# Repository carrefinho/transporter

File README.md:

# Transporter

Transporter is a low-profile V4N4G0N type keyboard with exploded bars, built around the $0.5 WCH CH32X035 MCU.

## Files

- [`transporter-pcb/`](transporter-pcb/): KiCad project
    - [Interactive BOM](transporter-pcb/bom/ibom.html)
    - [JLCPCB production files](transporter-pcb/jlcpcb/production_files/)
    - [View the PCB on KiCanvas](https://kicanvas.org/?github=https%3A%2F%2Fgithub.com%2Fcarrefinho%2Ftransporter%2Ftree%2Fmain%2Ftransporter-pcb)
- [`case/facade/`](case/facade/): Facade v4 case files

## Firmware

Find the ZMK module at [transporter-zmk-module](https://github.com/carrefinho/transporter-zmk-module)

## License

[CERN-OHL-P v2](LICENSE)

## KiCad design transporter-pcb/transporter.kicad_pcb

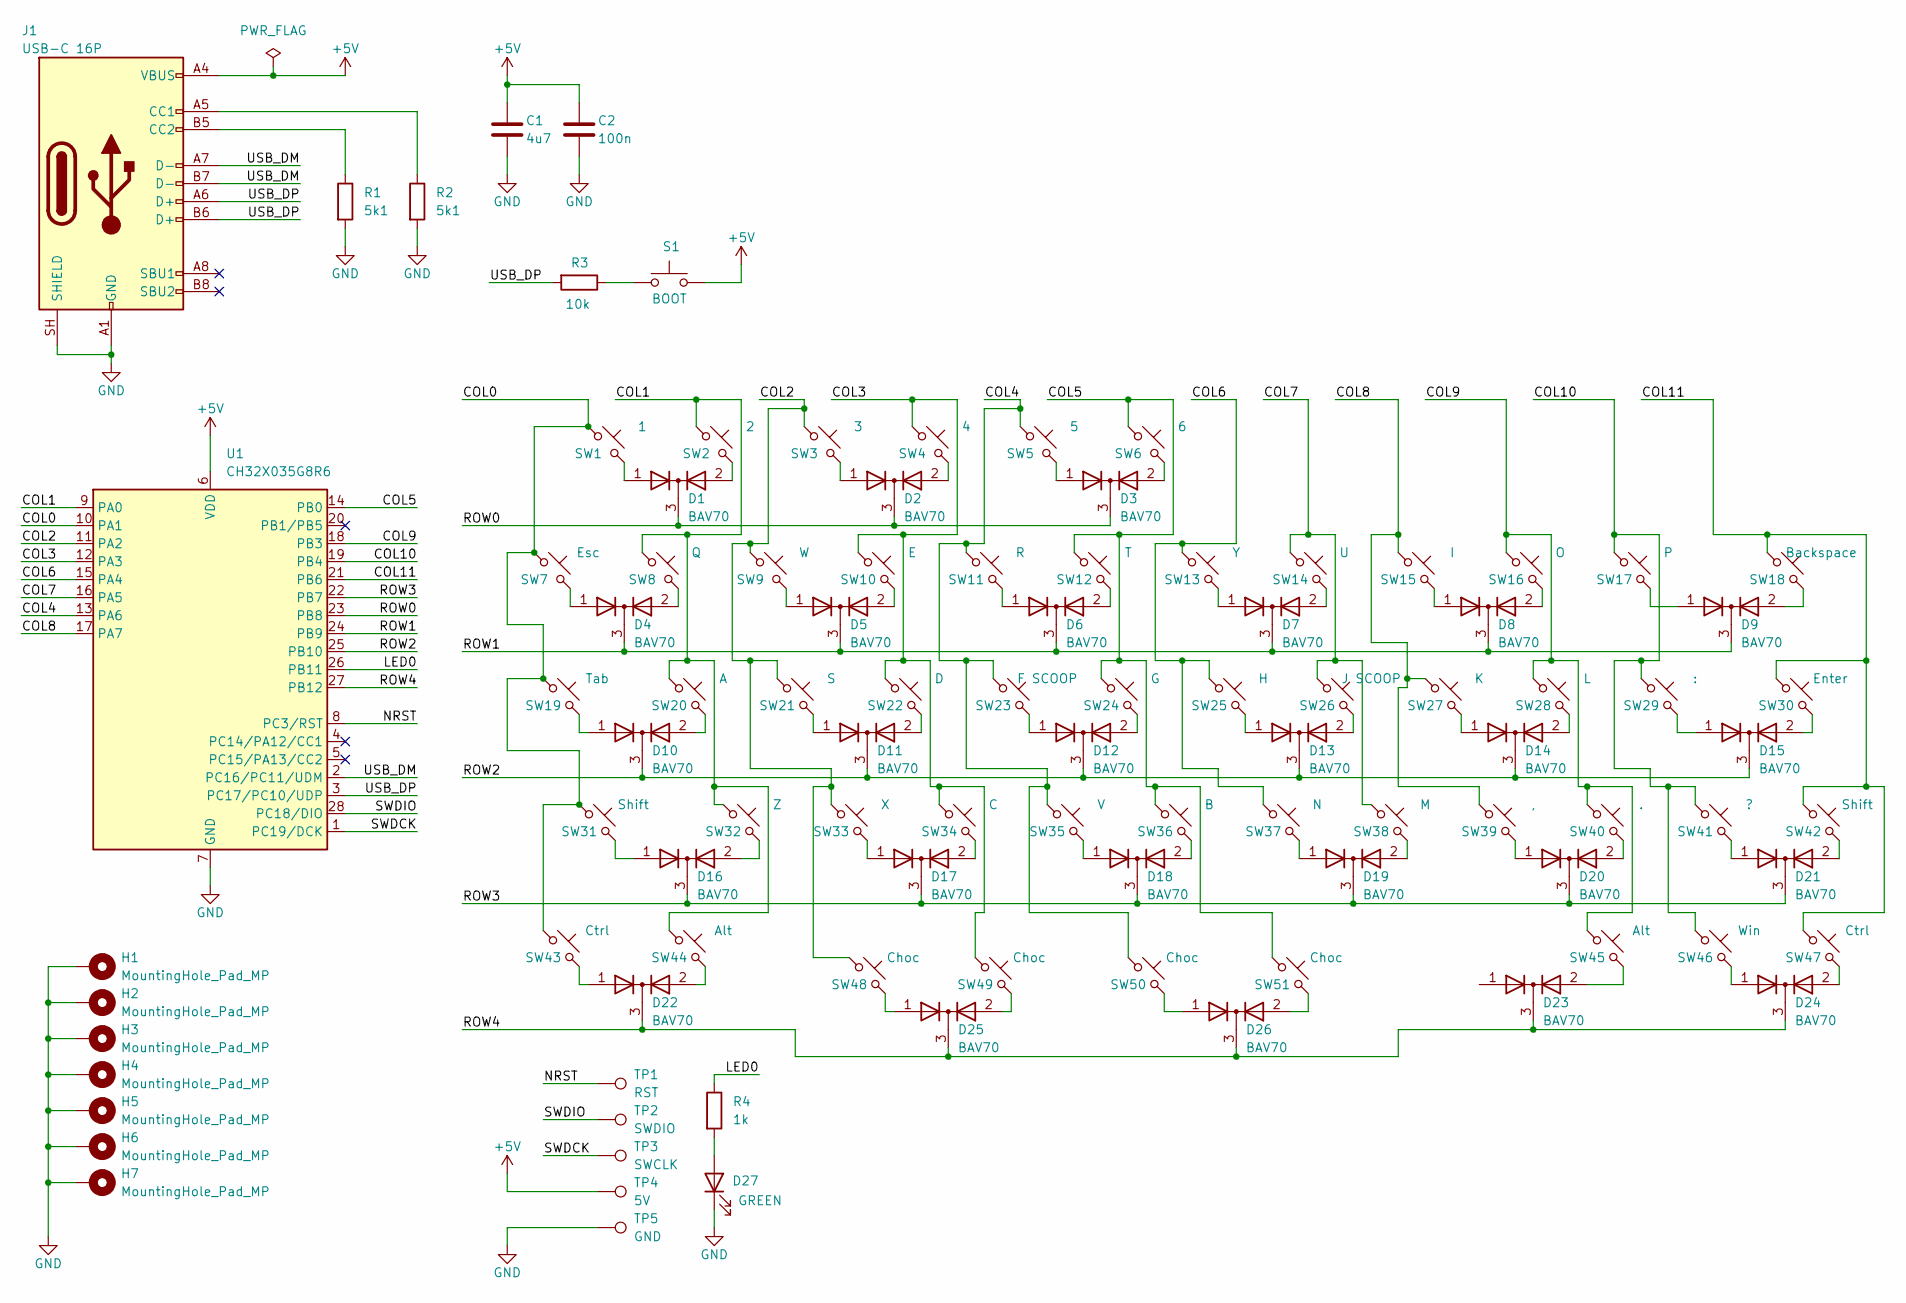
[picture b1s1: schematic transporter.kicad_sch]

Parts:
C1: 4u7; C_0805_2012Metric
C2: 100n; C_0603_1608Metric
D1, D2, D3, D4, D5, D6, D7, D8, D9, D10, D11, D12, D13, D14, D15, D16, D17, D18, D19, D20, D21, D22, D23, D24, D25, D26: BAV70; SOT-23
D27: GREEN; LED_0805_2012Metric
H1, H2, H3, H4, H5, H6, H7: MountingHole_Pad_MP; MountingHole_2.2mm_M2_Pad_TopBottom
J1: USB-C 16P; USB_C_Receptacle_G-Switch_GT-USB-7010ASV
R1, R2: 5k1; R_0603_1608Metric
R3: 10k; R_0603_1608Metric
R4: 1k; R_0603_1608Metric
S1: BOOT; SW_SPST_TS-1088-xR020
SW1: 1; SW_choc_v1v2_HS_19mmSpc
SW2: 2; SW_choc_v1v2_HS_19mmSpc
SW3: 3; SW_choc_v1v2_HS_19mmSpc
SW4: 4; SW_choc_v1v2_HS_19mmSpc
SW5: 5; SW_choc_v1v2_HS_19mmSpc
SW6: 6; SW_choc_v1v2_HS_19mmSpc
SW7: Esc; SW_choc_v1v2_HS_19mmSpc
SW8: Q; SW_choc_v1v2_HS_19mmSpc
SW9: W; SW_choc_v1v2_HS_19mmSpc
SW10: E; SW_choc_v1v2_HS_19mmSpc
SW11: R; SW_choc_v1v2_HS_19mmSpc
SW12: T; SW_choc_v1v2_HS_19mmSpc
SW13: Y; SW_choc_v1v2_HS_19mmSpc
SW14: U; SW_choc_v1v2_HS_19mmSpc
SW15: I; SW_choc_v1v2_HS_19mmSpc
SW16: O; SW_choc_v1v2_HS_19mmSpc
SW17: P; SW_choc_v1v2_HS_19mmSpc
SW18: Backspace; SW_choc_v1v2_HS_19mmSpc
SW19: Tab; SW_choc_v1v2_HS_19mmSpc
SW20: A; SW_choc_v1v2_HS_19mmSpc
SW21: S; SW_choc_v1v2_HS_19mmSpc
SW22: D; SW_choc_v1v2_HS_19mmSpc
SW23: F SCOOP; SW_choc_v1v2_HS_19mmSpc
SW24: G; SW_choc_v1v2_HS_19mmSpc
SW25: H; SW_choc_v1v2_HS_19mmSpc
SW26: J SCOOP; SW_choc_v1v2_HS_19mmSpc
SW27: K; SW_choc_v1v2_HS_19mmSpc
SW28: L; SW_choc_v1v2_HS_19mmSpc
SW29: :; SW_choc_v1v2_HS_19mmSpc
SW30: Enter; SW_choc_v1v2_HS_19mmSpc
SW31, SW42: Shift; SW_choc_v1v2_HS_19mmSpc
SW32: Z; SW_choc_v1v2_HS_19mmSpc
SW33: X; SW_choc_v1v2_HS_19mmSpc
SW34: C; SW_choc_v1v2_HS_19mmSpc
SW35: V; SW_choc_v1v2_HS_19mmSpc
SW36: B; SW_choc_v1v2_HS_19mmSpc
SW37: N; SW_choc_v1v2_HS_19mmSpc
SW38: M; SW_choc_v1v2_HS_19mmSpc
SW39: ,; SW_choc_v1v2_HS_19mmSpc
SW40: .; SW_choc_v1v2_HS_19mmSpc
SW41: ?; SW_choc_v1v2_HS_19mmSpc
SW43, SW47: Ctrl; SW_choc_v1v2_HS_19mmSpc
SW44, SW45: Alt; SW_choc_v1v2_HS_19mmSpc
SW46: Win; SW_choc_v1v2_HS_19mmSpc
SW48, SW49, SW50, SW51: Choc; SW_choc_v1v2_HS_19mmSpc
TP1: RST; TestPoint_Pad_D2.0mm
TP2: SWDIO; TestPoint_Pad_D2.0mm
TP3: SWCLK; TestPoint_Pad_D2.0mm
TP4: 5V; TestPoint_Pad_D2.0mm
TP5: GND; TestPoint_Pad_D2.0mm
U1: CH32X035G8R6; QSOP-28_3.9x9.9mm_P0.635mm

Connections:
+5V: C1.1, C2.1, J1.A4 (VBUS), J1.A9 (VBUS), J1.B4 (VBUS), J1.B9 (VBUS), S1.2, TP4.1 (1_1), U1.6 (VDD)
/COL0: SW1.1, SW7.1, SW19.1, SW31.1, SW43.1, U1.10 (PA1)
/COL1: SW2.1, SW8.1, SW20.1, SW32.1, SW44.1, U1.9 (PA0)
/COL2: SW3.1, SW9.1, SW21.1, SW33.1, SW48.1, U1.11 (PA2)
/COL3: SW4.1, SW10.1, SW22.1, SW34.1, SW49.1, U1.12 (PA3)
/COL4: SW5.1, SW11.1, SW23.1, SW35.1, SW50.1, U1.13 (PA6)
/COL5: SW6.1, SW12.1, SW24.1, SW36.1, SW51.1, U1.14 (PB0)
/COL6: SW13.1, SW25.1, SW37.1, U1.15 (PA4)
/COL7: SW14.1, SW26.1, SW38.1, U1.16 (PA5)
/COL8: SW15.1, SW27.1, SW39.1, U1.17 (PA7)
/COL9: SW16.1, SW28.1, SW40.1, SW45.1, U1.18 (PB3)
/COL10: SW17.1, SW29.1, SW41.1, SW46.1, U1.19 (PB4)
/COL11: SW18.1, SW30.1, SW42.1, SW47.1, U1.21 (PB6)
/LED0: R4.1, U1.26 (PB11)
/NRST: TP1.1 (1_1), U1.8 (PC3/RST)
/ROW0: D1.3 (K), D2.3 (K), D3.3 (K), U1.23 (PB8)
/ROW1: D4.3 (K), D5.3 (K), D6.3 (K), D7.3 (K), D8.3 (K), D9.3 (K), U1.24 (PB9)
/ROW2: D10.3 (K), D11.3 (K), D12.3 (K), D13.3 (K), D14.3 (K), D15.3 (K), U1.25 (PB10)
/ROW3: D16.3 (K), D17.3 (K), D18.3 (K), D19.3 (K), D20.3 (K), D21.3 (K), U1.22 (PB7)
/ROW4: D22.3 (K), D23.3 (K), D24.3 (K), D25.3 (K), D26.3 (K), U1.27 (PB12)
/SWDCK: TP3.1 (1_1), U1.1 (PC19/DCK)
/SWDIO: TP2.1 (1_1), U1.28 (PC18/DIO)
/USB_DM: J1.A7 (D-), J1.B7 (D-), U1.2 (PC16/PC11/UDM)
/USB_DP: J1.A6 (D+), J1.B6 (D+), R3.2, U1.3 (PC17/PC10/UDP)
GND: C1.2, C2.2, D27.1 (K), H1.MP, H2.MP, H3.MP, H4.MP, H5.MP, H6.MP, H7.MP, J1.A1 (GND), J1.A12 (GND), J1.B1 (GND), J1.B12 (GND), J1.SH (SHIELD), R1.2, R2.2, TP5.1 (1_1), U1.7 (GND)
unnamed: D1.1 (A), SW1.2
unnamed: D1.2 (A), SW2.2
unnamed: D2.1 (A), SW3.2
unnamed: D2.2 (A), SW4.2
unnamed: D3.1 (A), SW5.2
unnamed: D3.2 (A), SW6.2
unnamed: D4.1 (A), SW7.2
unnamed: D4.2 (A), SW8.2
unnamed: D5.1 (A), SW9.2
unnamed: D5.2 (A), SW10.2
unnamed: D6.1 (A), SW11.2
unnamed: D6.2 (A), SW12.2
unnamed: D7.1 (A), SW13.2
unnamed: D7.2 (A), SW14.2
unnamed: D8.1 (A), SW15.2
unnamed: D8.2 (A), SW16.2
unnamed: D9.1 (A), SW17.2
unnamed: D9.2 (A), SW18.2
unnamed: D10.1 (A), SW19.2
unnamed: D10.2 (A), SW20.2
unnamed: D11.1 (A), SW21.2
unnamed: D11.2 (A), SW22.2
unnamed: D12.1 (A), SW23.2
unnamed: D12.2 (A), SW24.2
unnamed: D13.1 (A), SW25.2
unnamed: D13.2 (A), SW26.2
unnamed: D14.1 (A), SW27.2
unnamed: D14.2 (A), SW28.2
unnamed: D15.1 (A), SW29.2
unnamed: D15.2 (A), SW30.2
unnamed: D16.1 (A), SW31.2
unnamed: D16.2 (A), SW32.2
unnamed: D17.1 (A), SW33.2
unnamed: D17.2 (A), SW34.2
unnamed: D18.1 (A), SW35.2
unnamed: D18.2 (A), SW36.2
unnamed: D19.1 (A), SW37.2
unnamed: D19.2 (A), SW38.2
unnamed: D20.1 (A), SW39.2
unnamed: D20.2 (A), SW40.2
unnamed: D21.1 (A), SW41.2
unnamed: D21.2 (A), SW42.2
unnamed: D22.1 (A), SW43.2
unnamed: D22.2 (A), SW44.2
unnamed: D23.2 (A), SW45.2
unnamed: D24.1 (A), SW46.2
unnamed: D24.2 (A), SW47.2
unnamed: D25.1 (A), SW48.2
unnamed: D25.2 (A), SW49.2
unnamed: D26.1 (A), SW50.2
unnamed: D26.2 (A), SW51.2
unnamed: D27.2 (A), R4.2
unnamed: J1.A5 (CC1), R2.1
unnamed: J1.B5 (CC2), R1.1
unnamed: R3.1, S1.1

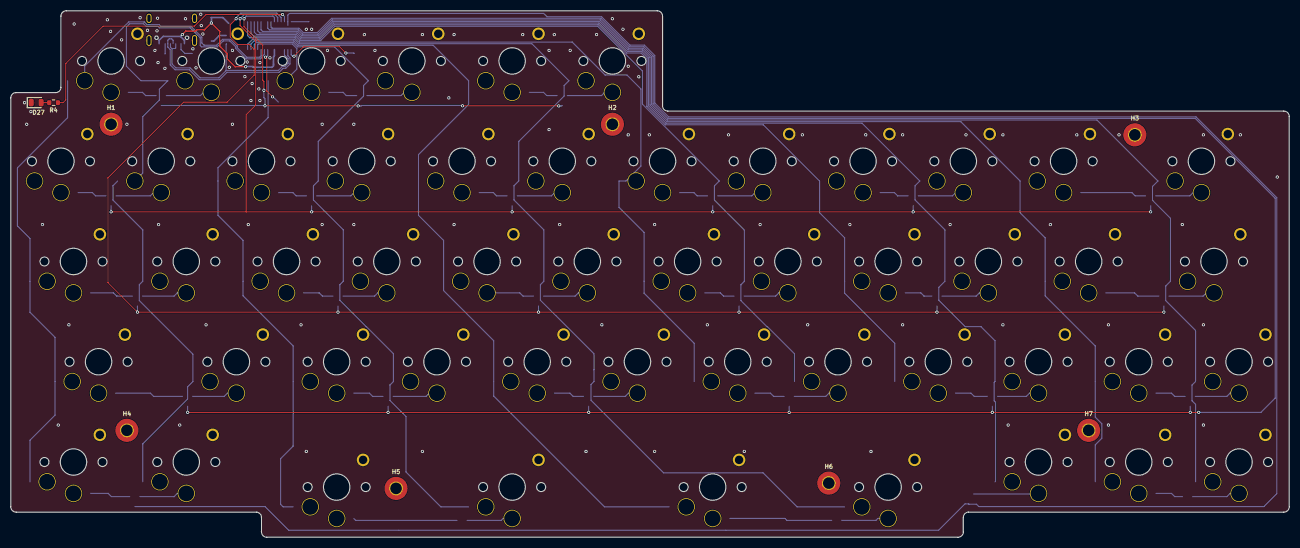
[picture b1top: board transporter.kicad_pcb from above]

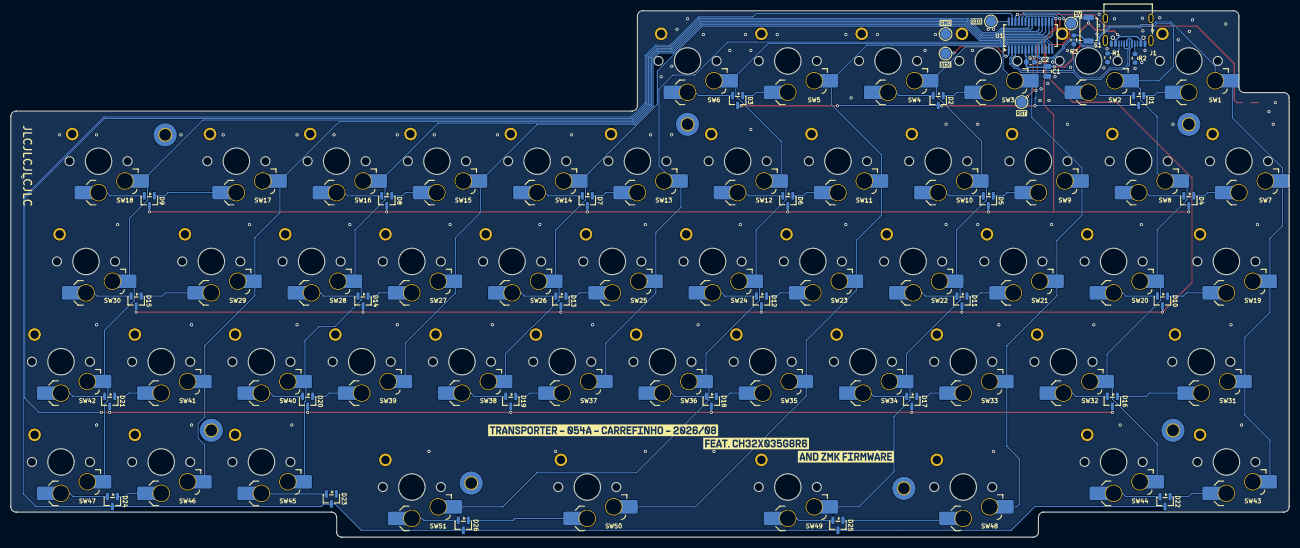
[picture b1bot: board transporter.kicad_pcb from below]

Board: 2 copper layers, 242.2 x 99.8 mm, 107 parts (98 on the bottom side), 80 nets.

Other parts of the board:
kibuzzard-6A81B6A9: G***; kibuzzard-6A81B6A9
kibuzzard-6A81B43D: G***; kibuzzard-6A81B43D
kibuzzard-6A81B44A: G***; kibuzzard-6A81B44A
kibuzzard-6A81B46A: G***; kibuzzard-6A81B46A
kibuzzard-6A81B62F: G***; kibuzzard-6A81B62F
kibuzzard-6A81B412: G***; kibuzzard-6A81B412
kibuzzard-6A81B455: G***; kibuzzard-6A81B455
kibuzzard-6A81B684: G***; kibuzzard-6A81B684

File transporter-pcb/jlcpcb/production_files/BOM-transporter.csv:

Comment,Designator,Footprint,LCSC,Quantity
CH32X035G8R6,U1,QSOP-28_3.9x9.9mm_P0.635mm,,1
1k,R4,R_0603_1608Metric,,1
GREEN,D27,LED_0805_2012Metric,,1
U,SW14,SW_choc_v1v2_HS_19mmSpc,,1
?,SW41,SW_choc_v1v2_HS_19mmSpc,,1
BAV70,D6,SOT-23,,1
BAV70,D20,SOT-23,,1
RST,TP1,TestPoint_Pad_D2.0mm,,1
D,SW22,SW_choc_v1v2_HS_19mmSpc,,1
Alt,SW45,SW_choc_v1v2_HS_19mmSpc,,1
Ctrl,SW47,SW_choc_v1v2_HS_19mmSpc,,1
5V,TP4,TestPoint_Pad_D2.0mm,,1
USB-C 16P,J1,USB_C_Receptacle_G-Switch_GT-USB-7010ASV,,1
BAV70,D26,SOT-23,,1
4u7,C1,C_0805_2012Metric,,1
BAV70,D8,SOT-23,,1
P,SW17,SW_choc_v1v2_HS_19mmSpc,,1
Z,SW32,SW_choc_v1v2_HS_19mmSpc,,1
GND,TP5,TestPoint_Pad_D2.0mm,,1
L,SW28,SW_choc_v1v2_HS_19mmSpc,,1
BOOT,S1,SW_SPST_TS-1088-xR020,,1
R,SW11,SW_choc_v1v2_HS_19mmSpc,,1
2,SW2,SW_choc_v1v2_HS_19mmSpc,,1
C,SW34,SW_choc_v1v2_HS_19mmSpc,,1
BAV70,D1,SOT-23,,1
Win,SW46,SW_choc_v1v2_HS_19mmSpc,,1
SWCLK,TP3,TestPoint_Pad_D2.0mm,,1
Choc,SW51,SW_choc_v1v2_HS_19mmSpc,,1
BAV70,D16,SOT-23,,1
:,SW29,SW_choc_v1v2_HS_19mmSpc,,1
BAV70,D11,SOT-23,,1
BAV70,D13,SOT-23,,1
S,SW21,SW_choc_v1v2_HS_19mmSpc,,1
Ctrl,SW43,SW_choc_v1v2_HS_19mmSpc,,1
10k,R3,R_0603_1608Metric,,1
BAV70,D15,SOT-23,,1
M,SW38,SW_choc_v1v2_HS_19mmSpc,,1
H,SW25,SW_choc_v1v2_HS_19mmSpc,,1
1,SW1,SW_choc_v1v2_HS_19mmSpc,,1
BAV70,D7,SOT-23,,1
Esc,SW7,SW_choc_v1v2_HS_19mmSpc,,1
BAV70,D10,SOT-23,,1
BAV70,D23,SOT-23,,1
Choc,SW50,SW_choc_v1v2_HS_19mmSpc,,1
F SCOOP,SW23,SW_choc_v1v2_HS_19mmSpc,,1
BAV70,D17,SOT-23,,1
N,SW37,SW_choc_v1v2_HS_19mmSpc,,1
Tab,SW19,SW_choc_v1v2_HS_19mmSpc,,1
BAV70,D3,SOT-23,,1
J SCOOP,SW26,SW_choc_v1v2_HS_19mmSpc,,1
A,SW20,SW_choc_v1v2_HS_19mmSpc,,1
BAV70,D25,SOT-23,,1
Backspace,SW18,SW_choc_v1v2_HS_19mmSpc,,1
BAV70,D5,SOT-23,,1
",",SW39,SW_choc_v1v2_HS_19mmSpc,,1
Choc,SW48,SW_choc_v1v2_HS_19mmSpc,,1
I,SW15,SW_choc_v1v2_HS_19mmSpc,,1
Q,SW8,SW_choc_v1v2_HS_19mmSpc,,1
E,SW10,SW_choc_v1v2_HS_19mmSpc,,1
O,SW16,SW_choc_v1v2_HS_19mmSpc,,1
BAV70,D4,SOT-23,,1
BAV70,D22,SOT-23,,1
Alt,SW44,SW_choc_v1v2_HS_19mmSpc,,1
W,SW9,SW_choc_v1v2_HS_19mmSpc,,1
Shift,SW42,SW_choc_v1v2_HS_19mmSpc,,1
T,SW12,SW_choc_v1v2_HS_19mmSpc,,1
X,SW33,SW_choc_v1v2_HS_19mmSpc,,1
K,SW27,SW_choc_v1v2_HS_19mmSpc,,1
BAV70,D18,SOT-23,,1
4,SW4,SW_choc_v1v2_HS_19mmSpc,,1
V,SW35,SW_choc_v1v2_HS_19mmSpc,,1
Choc,SW49,SW_choc_v1v2_HS_19mmSpc,,1
BAV70,D2,SOT-23,,1
5k1,R2,R_0603_1608Metric,,1
BAV70,D14,SOT-23,,1
5,SW5,SW_choc_v1v2_HS_19mmSpc,,1
G,SW24,SW_choc_v1v2_HS_19mmSpc,,1
Y,SW13,SW_choc_v1v2_HS_19mmSpc,,1
BAV70,D24,SOT-23,,1
BAV70,D21,SOT-23,,1
100n,C2,C_0603_1608Metric,,1
3,SW3,SW_choc_v1v2_HS_19mmSpc,,1
BAV70,D9,SOT-23,,1
SWDIO,TP2,TestPoint_Pad_D2.0mm,,1
Shift,SW31,SW_choc_v1v2_HS_19mmSpc,,1
B,SW36,SW_choc_v1v2_HS_19mmSpc,,1
Enter,SW30,SW_choc_v1v2_HS_19mmSpc,,1
5k1,R1,R_0603_1608Metric,,1
BAV70,D12,SOT-23,,1
6,SW6,SW_choc_v1v2_HS_19mmSpc,,1
BAV70,D19,SOT-23,,1
.,SW40,SW_choc_v1v2_HS_19mmSpc,,1
